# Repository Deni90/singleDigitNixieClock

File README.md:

# Single Digit Nixie Clock

A small project combining ESP32 with a vintage Soviet Nixie tube from the 70’ to create an artistic clock.
Originally developed on ESP8266/Arduino, now evolved to ESP32 with ESP-IDF for greater performance and stability.

Huge thank you to **[PCBWay](https://www.pcbway.com)** for sponsoring this project!

For more details follow project logs on: **[my personal blog](https://deni90.github.io/projects/singledigitnixieclock/)** or **[hackaday.io](https://hackaday.io/project/202115-single-digit-nixie-clock)**

Some of the key features:
- Shows current time (hours and minutes) on a single nixie tube.
- Configurable RGB LED backlight lights up the nixie tube every second.
- USB powered.
- Hosts a web server for easy setup & configuration.
- Synchronises time with NTP server.

Operating modes:
- AP mode
  - This mode is hosting a dedicated open wifi network called `NixieClock`. Its main purpose is to use it for first time setup to update wifi configuration. In addition, this mode will be activated when the clock is not able to connect to a configured network. Clock hosts a captive portal. A configuration page will be opened automatically upon connecting to `NixieClock` network.
- Client mode
  - In this mode the clock is connected to a configured wifi network. If there is internet access, the clock will synchronize its RTC with NTP server at startup and then every hour periodically.

In both modes, the configuration page is easily reachable on the following URL: `<HOSTNAME>.local`. There is no need to keep track of the IP address, the clock is hosting Multicast DNS (mDNS) server. mDNS is supported by Chrome and Safari browsers out of the box.

By default, the `HOSTNAME` is set to `mynixieclock`.

## Firmware

This project started on ESP8266 with the Arduino framework, which was great for fast prototyping. However, the reliance on third-party libraries often led to instability and crashes.

To ensure long-term support and stability, the project was migrated from the now-obsolete ESP8266 to the ESP32, using ESP-IDF in C++.

This move provides:
- A robust and stable firmware base.
- Full access to ESP32’s hardware features.
- Use of official ESP-IDF components

### REST API

| End point | Method | Body (JSON) | Description |
| - | - | - | - |
| /api/v1/led/led_info | GET | {<br>&nbsp;&nbsp;&nbsp;&nbsp;“R”: <0-255>,<br>&nbsp;&nbsp;&nbsp;&nbsp;“G”: <0-255>,<br>&nbsp;&nbsp;&nbsp;&nbsp;“B”: <0-255>,<br>&nbsp;&nbsp;&nbsp;&nbsp;“state”: <0-2><br>} | Get color and state of the backlight (RGB LED). |
| /api/v1/led/led_info | POST | {<br>&nbsp;&nbsp;&nbsp;&nbsp;“R”: <0-255>,<br>&nbsp;&nbsp;&nbsp;&nbsp;“G”: <0-255>,<br>&nbsp;&nbsp;&nbsp;&nbsp;“B”: <0-255>,<br>&nbsp;&nbsp;&nbsp;&nbsp;“state”: <0-2><br>} | Set color and state of the backlight (RGB LED). |
| /api/v1/clock/sleep_info | GET | {<br>&nbsp;&nbsp;&nbsp;&nbsp; “sleep_before”: \<value>,<br>&nbsp;&nbsp;&nbsp;&nbsp; “sleep_after”: \<value><br>} | Get sleep mode configuration. The time before and after (in minutes) the backlight will be turned off. |
| /api/v1/clock/sleep_info | POST | {<br>&nbsp;&nbsp;&nbsp;&nbsp; “sleep_before”: \<value>,<br>&nbsp;&nbsp;&nbsp;&nbsp; “sleep_after”: \<value><br>} | Set sleep mode configuration. |
| /api/v1/clock/time_info | GET | {<br>&nbsp;&nbsp;&nbsp;&nbsp;"tz_zone": "\<Geographic zone>",<br>&nbsp;&nbsp;&nbsp;&nbsp;“tz_offset”: “\<Proleptic TZ>",<br>&nbsp;&nbsp;&nbsp;&nbsp;"time_format": \<"12h" \| "24h"><br>} | Get time zone configuration |
| /api/v1/clock/time_info | POST | {<br>&nbsp;&nbsp;&nbsp;&nbsp;"tz_zone": "\<Geographic zone>",<br>&nbsp;&nbsp;&nbsp;&nbsp;“tz_offset”: “\<Proleptic TZ>",<br>&nbsp;&nbsp;&nbsp;&nbsp;"time_format": \<"12h" \| "24h"><br>} | Set time zone configuration |
| /api/v1/wifi/wifi_info | GET | {<br>&nbsp;&nbsp;&nbsp;&nbsp;"hostname": "\<HOSTNAME>",<br>&nbsp;&nbsp;&nbsp;&nbsp;“SSID”: “\<Wifi SSID>”,<br>&nbsp;&nbsp;&nbsp;&nbsp;"auth_type": \<"open" \| "wpa2" \| "wpa3">,<br>&nbsp;&nbsp;&nbsp;&nbsp;“password”: “\<base64 encoded password>”<br>} | Get wifi configuration. |
| /api/v1/wifi/wifi_info | POST | {<br>&nbsp;&nbsp;&nbsp;&nbsp;"hostname": "\<HOSTNAME>",<br>&nbsp;&nbsp;&nbsp;&nbsp;“SSID”: “\<Wifi SSID>”,<br>&nbsp;&nbsp;&nbsp;&nbsp;"auth_type": \<"open" \| "wpa2" \| "wpa3">,<br>&nbsp;&nbsp;&nbsp;&nbsp;“password”: “\<base64 encoded password>”<br>} | Set wifi configuration. | Set wifi configuration. |

### Front-end layout & design

Initially, the front end was implemented with jQuery mobile. Reason for choosing this framework was in its simplicity. It provides a simple way to create and control user interface components. One thing that always annoyed me was its low response time. It took too much time to load jQuery, jQueryMobile and theme resources. On top of this, this slow response time caused WDT resets.

One more thing, I just realised that  jQuery mobile project is deprecated since October 7, 2021. Huh, when it comes to web related technologies, it looks like I'm living under a rock...

To solve these issues, I opted to completely re implement the frontend using plain HTML, CSS and JavaScript. The end result looks almost the same as the previous design or even better. Responsiveness and stability increased significantly. The only drawback is now in maintenance and extension. It is required to implement everything manually.

## Design

Schematic and PCB are designed with KiCAD

### Control board

Control board is basically a re-packaged generic ESP32 board design connected with DS3231 real time clock and NCH8200HV high voltage boost module board.

#### Schematic

### Display board

Display board uses a CD4028 BCD-to-decimal decoder. Its purpose is to reduce the number of required GPIO pins from 10 to just 4 for showing digits from 0 to 9. Compared to dedicated BCD to decimal decoder nixie drivers (like K511ID1), the CD4028 is a widely spread component and it is available in SMD package. Since CD4028 has a voltage range from 3.0V to 15V it is not compatible with nixie tube’s operating voltage of 170V out of the box. This problem is solved with MMBTA42, a high voltage transistor, rated to more than 200V.

The rest of the display board consists of a WS2812B RGB LED and a pin header used to connect with the control board.

#### Schematic

## PCB manufacturing

A representative from **PCBWay** contacted me because he was deeply impressed by my project and offered to sponsor a batch of PCBs to test out their services.

Since I recently moved to KiCad, it was a perfect opportunity to try out the PCBWay Plug-in for KiCad. It provides a simple way to place an order in just a few clicks. There is no need to bother with exporting gerber files, everything is automated. You just need to update the PCB specification and fill in the shipping information on the webpage. That’s it.

The entire journey from placing the order to receiving the package took less than a week. Incredible! PCBWay did a superb job, PCBs are amazing. I am more than impressed.

## Enclosure design

3D model is made with Autodesk Fusion 360.

The end result is a simple box shaped design with holes for the nixie tube and USB connector.

## Third-party dependencies

This project includes `firmware/flash_data/frontend/zones.json` from https://github.com/nayarsystems/posix_tz_db, licensed under the MIT License.

## Resources

* [IN-14 Nixie tube datasheet](https://tubehobby.com/datasheets/in14.pdf)
* [NCH8200HV High Voltage DC-DC Booster module](http://omnixie.io/nch8200hv.html)
* [CD4028 datasheet](https://www.renesas.com/en/document/dst/cd4028bms-datasheet?srsltid=AfmBOoqU2NILPd5EzyLmpNgOihDv6LZo1jPMcaXfnR6dCclXbg2DF4TL)

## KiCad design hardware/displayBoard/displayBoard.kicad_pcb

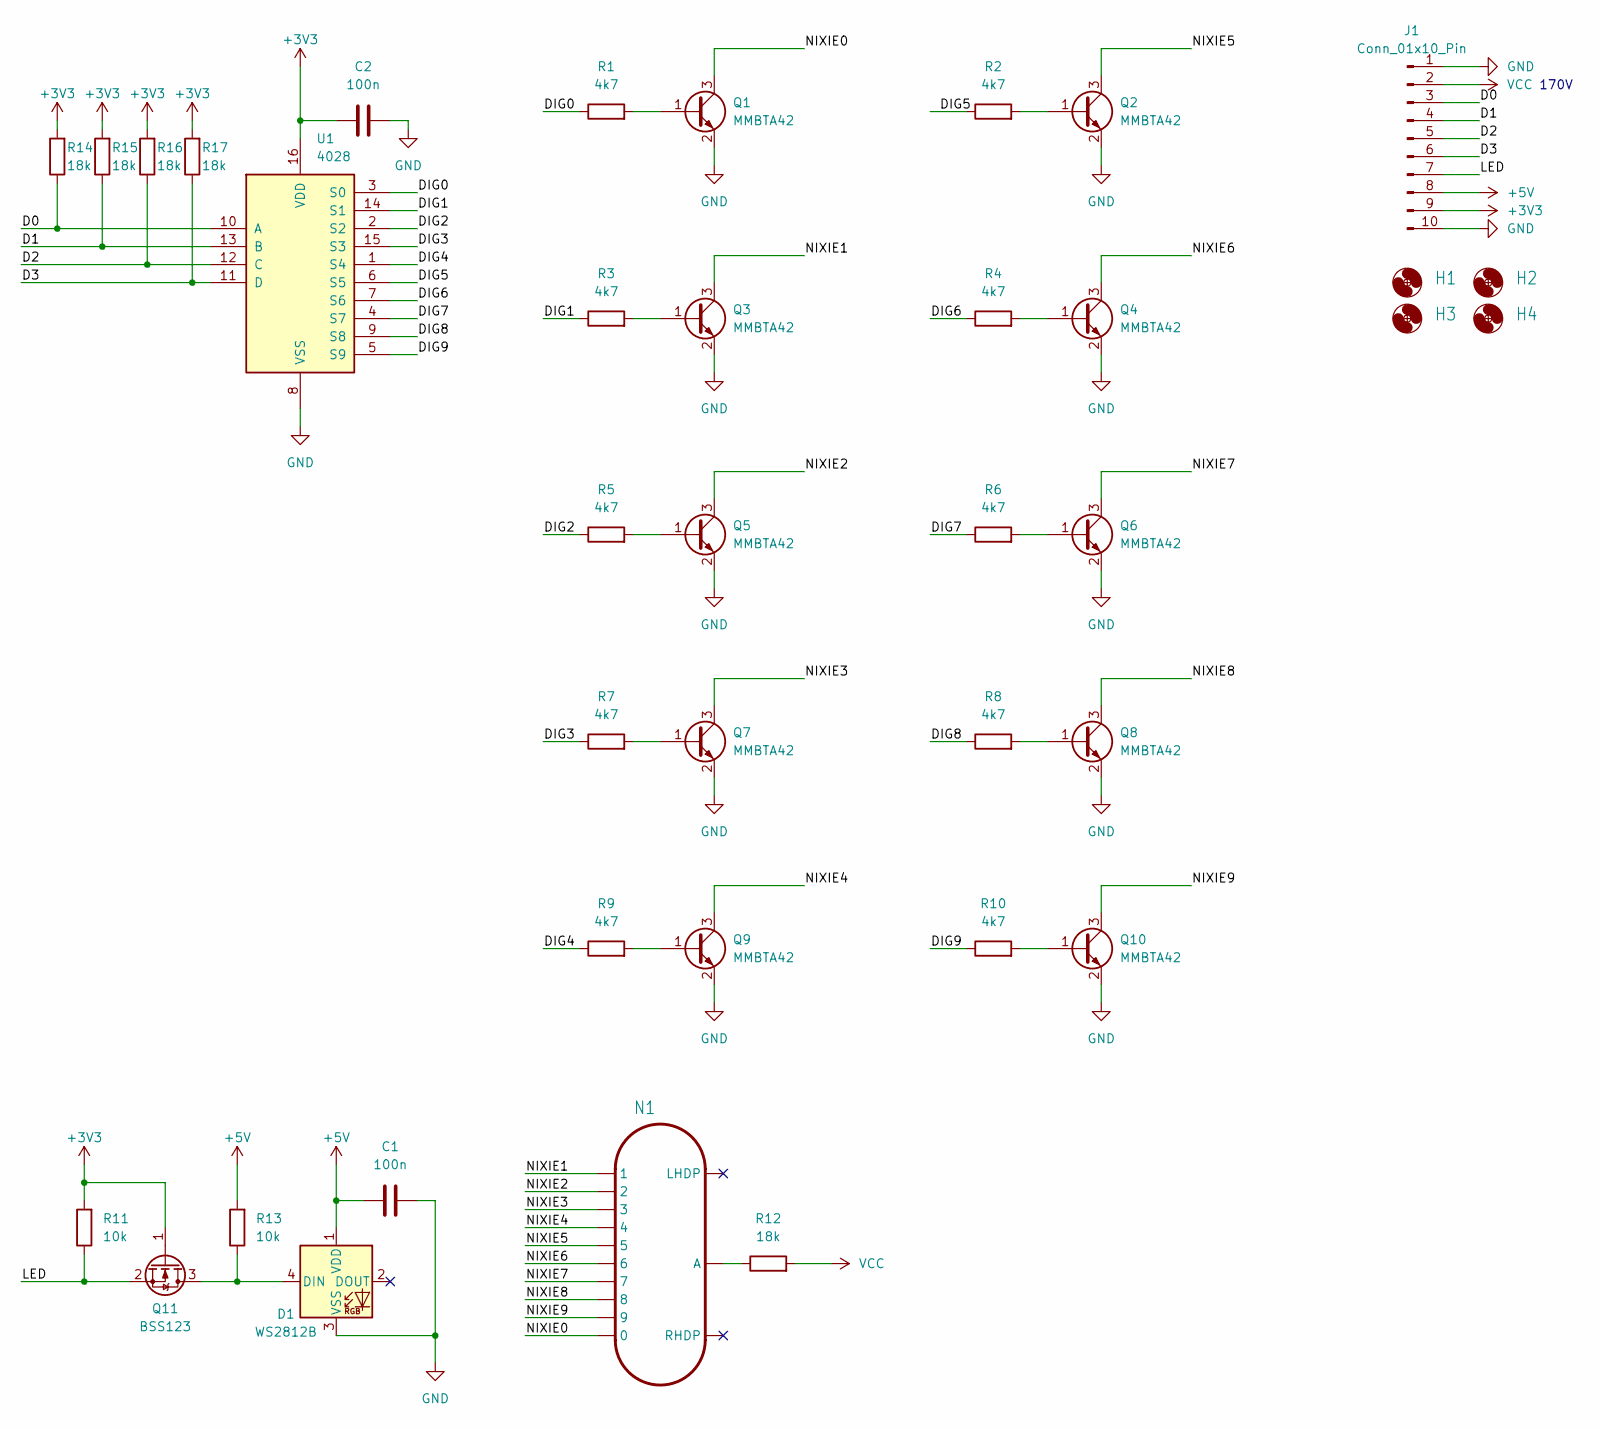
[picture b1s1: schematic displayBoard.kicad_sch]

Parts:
C1, C2: 100n; C_0603_1608Metric
D1: WS2812B; LED_WS2812B_PLCC4_5.0x5.0mm_P3.2mm
H1, H2, H3, H4: MountingHole_3.2mm_M3
J1: Conn_01x10_Pin; PinHeader_1x10_P2.54mm_Vertical
N1: IN-14
Q1, Q2, Q3, Q4, Q5, Q6, Q7, Q8, Q9, Q10: MMBTA42; SOT-23
Q11: BSS123; SOT-23
R1, R2, R3, R4, R5, R6, R7, R8, R9, R10: 4k7; R_0603_1608Metric
R11, R13: 10k; R_0603_1608Metric
R12, R14, R15, R16, R17: 18k; R_0603_1608Metric
U1: 4028; SO-16_3.9x9.9mm_P1.27mm

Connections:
+3V3: C2.1, J1.9, Q11.1 (G), R11.2, R14.2, R15.2, R16.2, R17.2, U1.16 (VDD)
+5V: C1.1, D1.1 (VDD), J1.8, R13.2
/D0: J1.3, R14.1, U1.10 (A)
/D1: J1.4, R15.1, U1.13 (B)
/D2: J1.5, R16.1, U1.12 (C)
/D3: J1.6, R17.1, U1.11 (D)
/DIG0: R1.1, U1.3 (S0)
/DIG1: R3.1, U1.14 (S1)
/DIG2: R5.1, U1.2 (S2)
/DIG3: R7.1, U1.15 (S3)
/DIG4: R9.1, U1.1 (S4)
/DIG5: R2.1, U1.6 (S5)
/DIG6: R4.1, U1.7 (S6)
/DIG7: R6.1, U1.4 (S7)
/DIG8: R8.1, U1.9 (S8)
/DIG9: R10.1, U1.5 (S9)
/LED: J1.7, Q11.2 (S), R11.1
/NIXIE0: N1.0, Q1.3 (C)
/NIXIE1: N1.1, Q3.3 (C)
/NIXIE2: N1.2, Q5.3 (C)
/NIXIE3: N1.3, Q7.3 (C)
/NIXIE4: N1.4, Q9.3 (C)
/NIXIE5: N1.5, Q2.3 (C)
/NIXIE6: N1.6, Q4.3 (C)
/NIXIE7: N1.7, Q6.3 (C)
/NIXIE8: N1.8, Q8.3 (C)
/NIXIE9: N1.9, Q10.3 (C)
GND: C1.2, C2.2, D1.3 (VSS), J1.1, J1.10, Q1.2 (E), Q2.2 (E), Q3.2 (E), Q4.2 (E), Q5.2 (E), Q6.2 (E), Q7.2 (E), Q8.2 (E), Q9.2 (E), Q10.2 (E), U1.8 (VSS)
unnamed: D1.4 (DIN), Q11.3 (D), R13.1
unnamed: N1.A, R12.1
unnamed: Q1.1 (B), R1.2
unnamed: Q2.1 (B), R2.2
unnamed: Q3.1 (B), R3.2
unnamed: Q4.1 (B), R4.2
unnamed: Q5.1 (B), R5.2
unnamed: Q6.1 (B), R6.2
unnamed: Q7.1 (B), R7.2
unnamed: Q8.1 (B), R8.2
unnamed: Q9.1 (B), R9.2
unnamed: Q10.1 (B), R10.2
VCC: J1.2, R12.2

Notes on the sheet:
170V

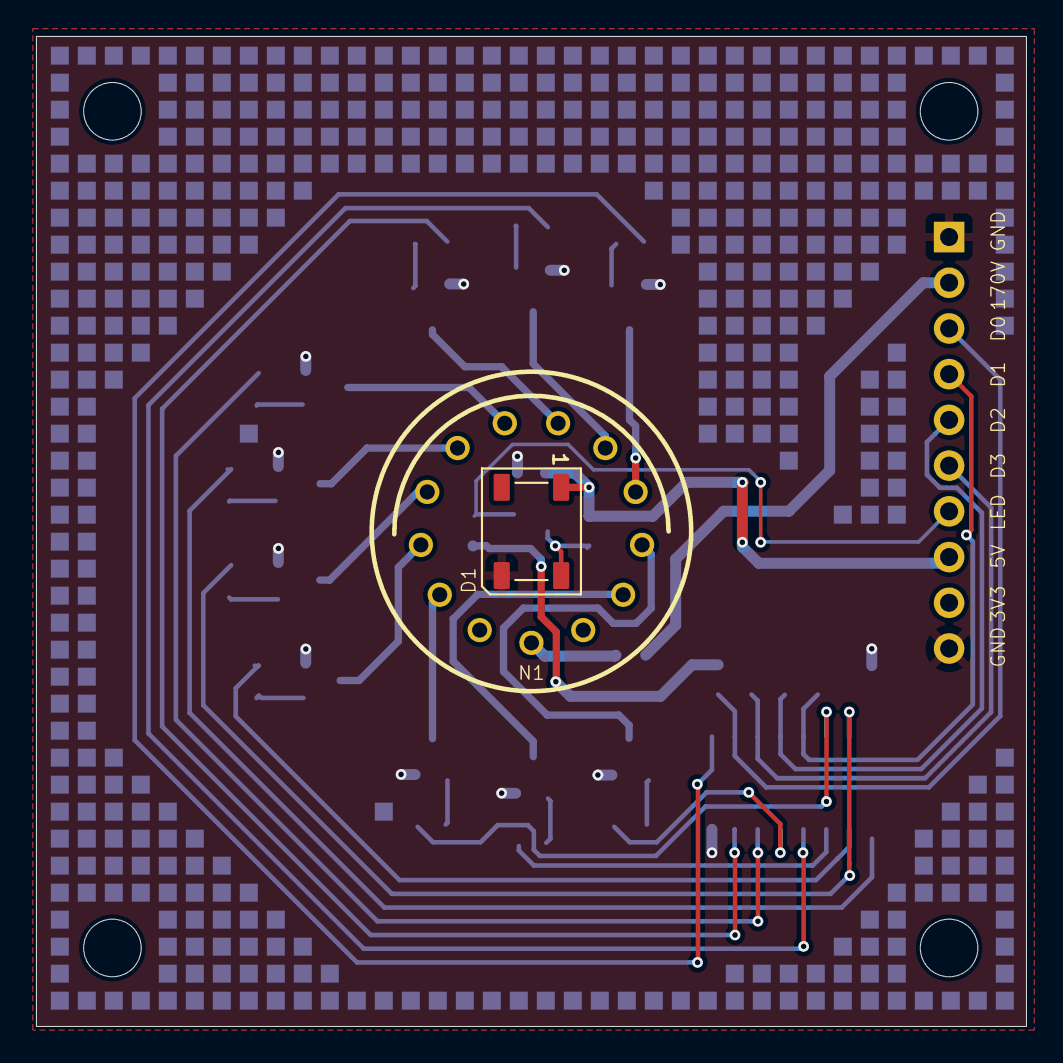
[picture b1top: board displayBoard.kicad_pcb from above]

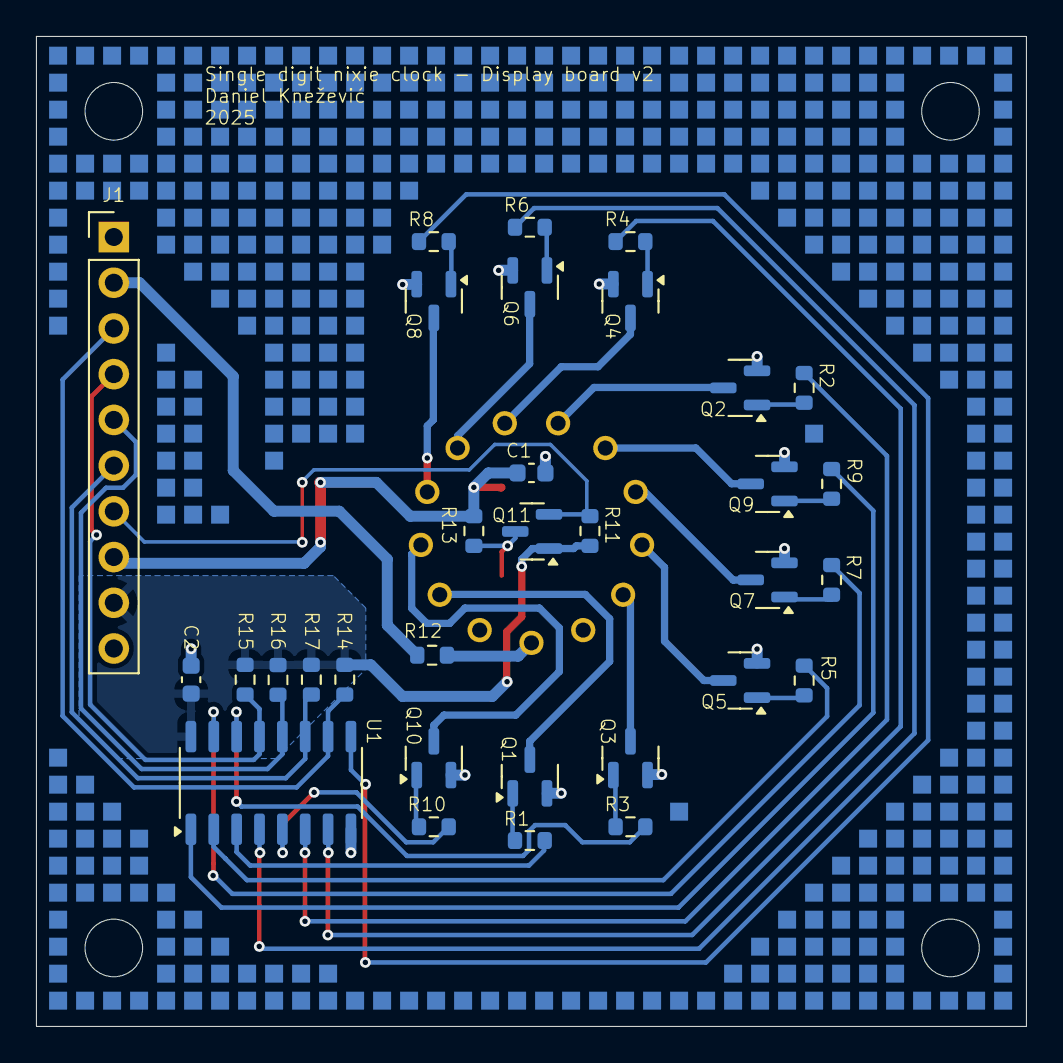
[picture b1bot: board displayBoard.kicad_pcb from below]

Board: 2 copper layers, 55.0 x 55.0 mm, 38 parts (32 on the bottom side), 41 nets.

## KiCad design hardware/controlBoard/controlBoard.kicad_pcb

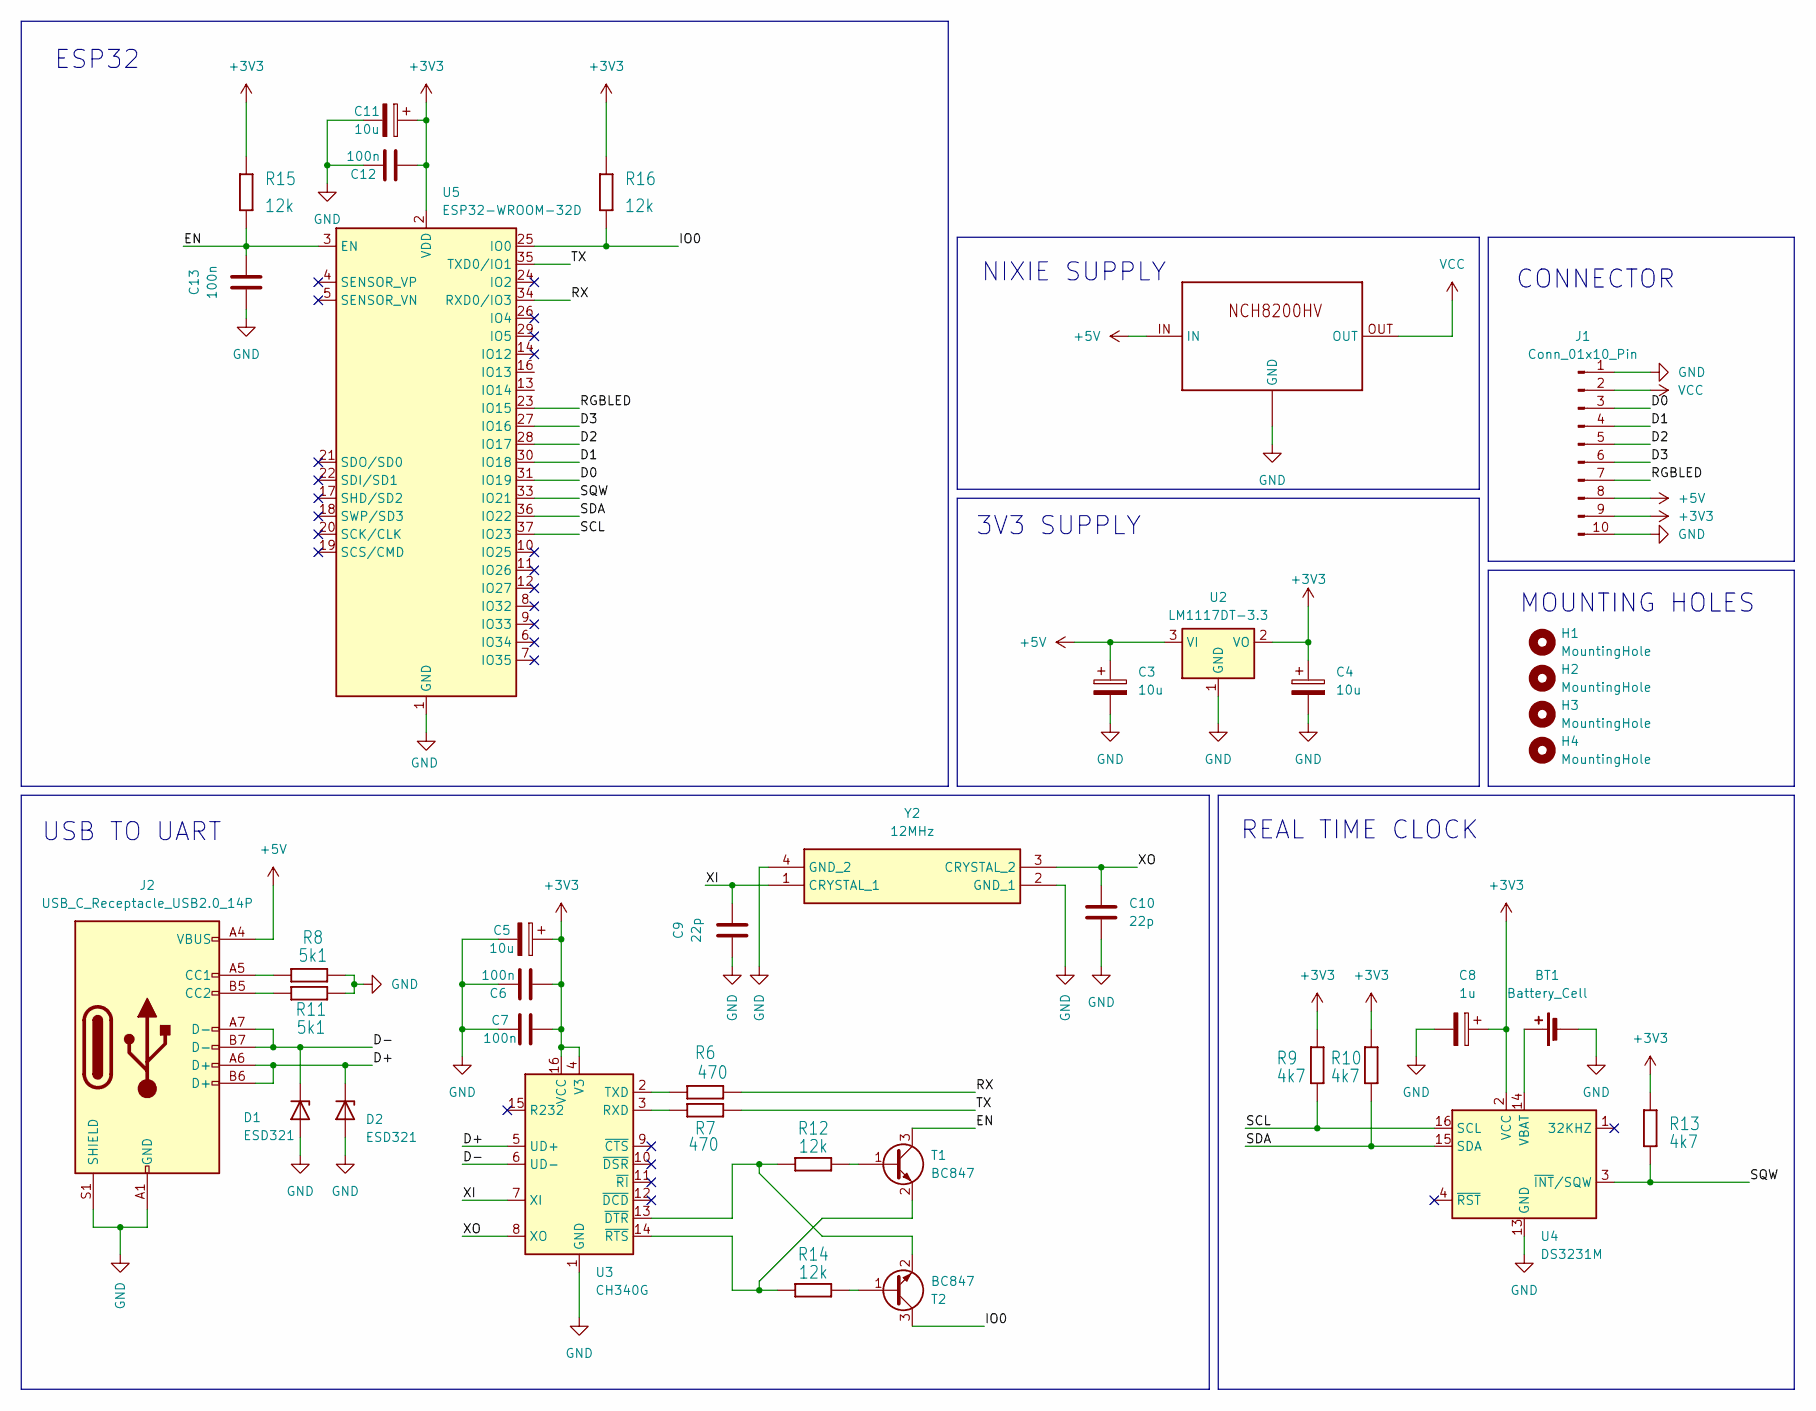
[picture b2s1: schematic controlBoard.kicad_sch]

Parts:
BT1: Battery_Cell; BatteryHolder_MYOUNG_BS-07-A1BJ001_CR2032
C3, C4, C5, C11: 10u; CP_EIA-3216-10_Kemet-I
C6, C7, C12, C13: 100n; C_0603_1608Metric
C8: 1u; CP_EIA-3216-10_Kemet-I
C9, C10: 22p; C_0603_1608Metric
D1, D2: ESD321; D_SOD-523
H1, H2, H3, H4: MountingHole; MountingHole_3.2mm_M3
J1: Conn_01x10_Pin; PinHeader_1x10_P2.54mm_Vertical
J2: USB_C_Receptacle_USB2.0_14P; USB_C_Receptacle_GCT_USB4105-xx-A_16P_TopMnt_Horizontal
R6, R7: 470; R_0603_1608Metric
R8, R11: 5k1; R_0603_1608Metric
R9, R10, R13: 4k7; R_0603_1608Metric
R12, R14, R15, R16: 12k; R_0603_1608Metric
T1, T2: BC847; SOT-23
U2: LM1117DT-3.3; TO-252-3_TabPin2
U3: CH340G; SOIC-16_3.9x9.9mm_P1.27mm
U4: DS3231M; SOIC-16W_7.5x10.3mm_P1.27mm
U5: ESP32-WROOM-32D; ESP32-WROOM-32D-no-keepout
UNK1: NCH8200HV
Y2: 12MHz; 405I35D25M00000; Mouser Part Number 774-405I35D25M00000

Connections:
+3V3: C4.1, C5.1, C6.1, C7.2, C8.1, C11.1, C12.1, J1.9, R9.2, R10.2, R13.2, R15.2, R16.2, U2.2 (VO), U3.4 (V3), U3.16 (VCC), U4.2 (VCC), U5.2 (VDD)
+5V: C3.1, J1.8, J2.A4 (VBUS), J2.A9 (VBUS), J2.B4 (VBUS), J2.B9 (VBUS), U2.3 (VI), UNK1.IN
/D0: J1.3, U5.31 (IO19)
/D1: J1.4, U5.30 (IO18)
/D2: J1.5, U5.28 (IO17)
/D3: J1.6, U5.27 (IO16)
/D+: D2.1 (K), J2.A6 (D+), J2.B6 (D+), U3.5 (UD+)
/D-: D1.1 (K), J2.A7 (D-), J2.B7 (D-), U3.6 (UD-)
/EN: C13.1, R15.1, T1.3 (C), U5.3 (EN)
/IO0: R16.1, T2.3 (C), U5.25 (IO0)
/RGBLED: J1.7, U5.23 (IO15)
/RX: R6.2, U5.34 (RXD0/IO3)
/SCL: R9.1, U4.16 (SCL), U5.37 (IO23)
/SDA: R10.1, U4.15 (SDA), U5.36 (IO22)
/SQW: R13.1, U4.3 (~INT/SQW), U5.33 (IO21)
/TX: R7.2, U5.35 (TXD0/IO1)
/XI: C9.1, U3.7 (XI), Y2.1 (CRYSTAL_1)
/XO: C10.1, U3.8 (XO), Y2.3 (CRYSTAL_2)
GND: BT1.2 (-), C3.2, C4.2, C5.2, C6.2, C7.1, C8.2, C9.2, C10.2, C11.2, C12.2, C13.2, D1.2 (A), D2.2 (A), J1.1, J1.10, J2.A1 (GND), J2.A12 (GND), J2.B1 (GND), J2.B12 (GND), J2.S1 (SHIELD), R8.2, R11.2, U2.1 (GND), U3.1 (GND), U4.5 (GND), U4.6 (GND), U4.7 (GND), U4.8 (GND), U4.9 (GND), U4.10 (GND), U4.11 (GND), U4.12 (GND), U4.13 (GND), U5.1 (GND), U5.15 (GND), U5.38 (GND), U5.39 (GND), UNK1.GND@1 (GND), UNK1.GND@2 (GND), Y2.2 (GND_1), Y2.4 (GND_2)
unnamed: BT1.1 (+), U4.14 (VBAT)
unnamed: J2.A5 (CC1), R8.1
unnamed: J2.B5 (CC2), R11.1
unnamed: R12.2, T1.1 (B)
unnamed: R14.1, T1.2 (E), U3.14 (~RTS)
unnamed: R14.2, T2.1 (B)
unnamed: R12.1, T2.2 (E), U3.13 (~DTR)
unnamed: R7.1, U3.3 (RXD)
unnamed: R6.1, U3.2 (TXD)
VCC: J1.2, UNK1.OUT

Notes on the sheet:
ESP32
CONNECTOR
NIXIE SUPPLY
USB TO UART
3V3 SUPPLY
REAL TIME CLOCK
MOUNTING HOLES

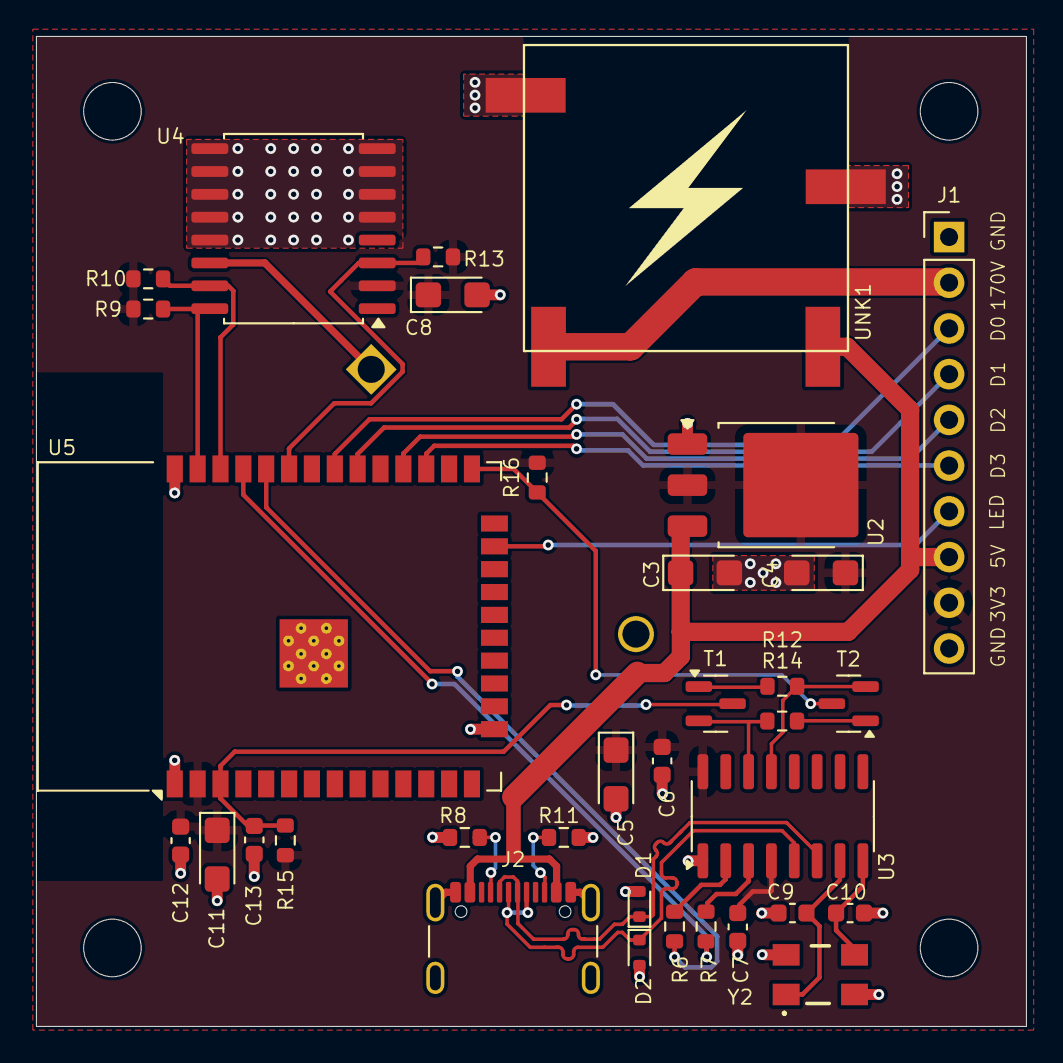
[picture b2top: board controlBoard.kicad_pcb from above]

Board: 2 copper layers, 55.0 x 55.0 mm, 39 parts (1 on the bottom side), 29 nets.

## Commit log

2020-04-23 Updated README file
2020-05-06 Refactored usage of timers and enabled SQW of DS3231
    - changed led pin to D3
    - enabled interrupt for SQW
2020-05-06 Renamed UpdateState to Update in LedController.
2020-05-06 Implemented BCD 2 decimal decoder
2022-04-01 Added display board schematic & PCB design
2022-04-01 Moved displayBoard under schematic folder
2022-04-06 Removed white spaces from LedController
2022-04-06 Separated led info from led controller
    Led information like color and state are moved to a separate module.
2022-04-06 EEPROM hangling is moved under ConfigStore module
    Config store module is responsible for loading and saving device's
    configurations like led color, led status, ...
2022-04-06 Created ClockFace module to handle time animations.
    Main has been refactored by moving nixie & led handling into a
    sepatare module.
2022-04-06 Adafruit_NeoPixel is moved under LedController
2022-04-06 Defines converted to constexpr & added splash screen
2022-04-07 Updated LedState to have ON, OFF and FADE states
2022-04-11 Removed vscode folder
2022-04-11 Implemented a web server by using jquery mobile
    - REST server has been replaced by ESP8266WebServer
    - Web page is stored on flash by using LittleFS file system
    - Backlight control has been implemented with ClockInterface
2022-04-12 Implemented set color in web server
2022-04-12 Refactored LED handling
    - removed alpha from classes and interfaces
    - fading is simplified by modifying only the brightness
2023-12-27 Create an adapter to fix showing wrong digits
    Create In18NixieTube to adapt BCD2DecimalDecoder so that correct
    digits are shown on the nixie tube.
    For some reason the pinout of the IN-18 tube does not match with
    Eagle's component.
2023-12-27 Fine tune animation timeouts and reverse intro
2023-12-28 Reformat code
2023-12-28 Move source to firmware folder
2023-12-28 Add backlight configuration to server
    - enable setting backlight brightness, mode and color
2023-12-28 Add set current time to REST API
2023-12-28 Add clang-format & reformat code
2023-12-29 Refactor WebServer
    - Replace ESP8266WebServer with AsyncWebServer
    - Simplify module by removing singleton
2023-12-29 Add an option for pulsing LED
2023-12-29 Remove AlwaysBreakAfterReturnType from clang-format
2023-12-29 Make truthTable const
2023-12-29 Remove formatSwitch from HTML page
2023-12-29 Show time after it is updated via REST API
    - Refactor ClockFace to accept the number of repeats whren showing time
2023-12-30 Rename In18NixieTube module to In14NixieTube
2024-01-03 Reduce the size of the controll board
2024-01-03 Add README & images to CB
2024-01-03 Add control board schematic
2024-02-01 Supply CH340 with 3V3 to fix ESP programming issue
    In order to properly communicate with ESP it is required to use CH340
    USB to serial in 3V3 mode.
2024-02-02 Add ESD protection to USB data lanes
2024-02-02 Add title to PCBs
2024-02-02 Update schematic images
2024-10-07 Add doxygen comments
2024-10-07 Remove ci variable
2024-10-07 Refactor In14NixieTube by encapsulating BCD2DecimalDecoder
2024-10-07 Change SSID
2024-10-10 Simplify WebServer by combining paths
    - Combine backlight related paths into Get/Set methods.
    - Add lock to led controller to prevent updating led state while showing
    time.
    - Update index.html to use the new REST API.
2024-10-10 Rename counter to secondsCounter and fix buffer size
2024-10-16 Refactor HandleGetLedInfo
    - Use JsonDocument instead of StaticJsonDocument
    - Use String instead of char buffer
    - Use serializeJson instead of serializeJsonPretty to shorten the JSON
    message
2024-10-16 Move ShowTime to HandleInterrupt interrupt routine
2024-10-28 Rename label to Color preview
2024-10-31 Move implementation of ClockInterface to NixieClock
    - Move implementation of ClockInterface to ClockFace
    - Remove NixieClockInterface class
    - Rename ClockFace class to NixieClock
2024-11-01 Add headings to tabs
2024-11-01 Fix OnGetLedInfo to get info from ConfigStore
2024-11-01 Update time format in prints
2024-11-01 Check for NULL in WebServer::Handle functions
2024-11-01 Rename backlight to ledInfo
2024-11-02 Implement sleep mode feature
    Sleep mode turns off the led and nixie tube for a configured time period
2024-11-02 Rename Load/StoreLedConfiguration to Load/StoreLedInfo
2024-11-02 Fix updating led info while in sleep mode
2024-11-05 Add readme file to the project
2024-11-17 Replace image with gif
2024-11-18 Update readme files
2024-12-28 Update dependencies
2024-12-28 Refactor ConfigStore to use LittleFS
    - Replace EEPROM with json config files
2024-12-28 Add ToJson() to LedInfo and SleepInfo classes
    - Update ConfigStore and WebServer to use ToJson().
2024-12-28 Make prints in setup() pretty
2024-12-28 Load Wifi SSID and password from a JSON file
2024-12-28 Move web server files to a dedicated folder
2024-12-28 Add wifi tab to web page
    - Extend ConfigStore with SaveWifiInfo function.
    - Extend WebServer with /wifi GET and POST methods.
    - Update web page with a wifi tab.
2024-12-28 Fix colorBox init and currentTime label access
2024-12-30 Update firmware's readme file
2025-01-01 Add more comments to NixieClock::Handle
2025-01-01 Convert EaglePCB projects to KiCad
2025-01-06 Connect clock to a local wifi network
    - By default configure clock to use wifi in station mode.
    - Try to connect to the configured wifi network
    - If it is not possible to connect to a configured network switch to AP mode
    - Use different DnsServer for captive portal in AP mode
    - Use MDNS for station mode
2025-01-06 Remove 'ap' prefix from wifi tab
2025-01-07 Synchronise time via NTP
    - Create TimeInfo for storing time related configuration
    - Create TimeManager for getting time from NTP server
2025-01-07 Make time zone configurable via web server
2025-01-07 Remove printing out config and remove default wifi credentials
2025-01-11 Re-implement web server to improve performance and stability
    - Remove dependency to jQuery mobile
    - Use plain javascript for the front-end implementation
    - Define a cutom css style to follow existing UI design
    - Refactor WebServer REST api handling to use AsyncCallbackJsonWebHandler
    - Enable mDNS in AP mode
2025-01-11 Use usb type C connector and re-wire control board with KiCad components
2025-01-11 Remove formatting from config files
2025-01-11 Refactor *DNS usage
2025-01-12 Enter sleep mode right after config is updated
2025-01-12 Modify SleepInfo to use minutes and update frontend
2025-01-12 Re-wire control display with KiCad components
2025-01-12 Update images of new PCBs
2025-01-12 Update main readme file
2025-01-13 Add front-end section to README
2025-01-14 Describe operating modes
2025-01-16 Update control board with updated usb-c wiring
2025-01-18 Make hostname configurable via web app
2025-01-22 Add model diagrams to Readme
2025-01-30 Fix weird behaviour of the LED by adding a level shifter to DIN pin
2025-01-31 Match via sizes between two PCBs
2025-02-11 Update README with hackaday link and PCBWay sponsorship
2025-02-28 Add enclosure model to repo
2025-03-30 Replace agdl/Base64 with densaugeo/base64 library
2025-03-30 Replace PlatformIO with Makefile
    To simplify project setup, the Arduino core for ESP8266 and all dependencies are moved to be part of the project as git submodules. This way, there is no need to manualy download and setup Arduino ID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
2025-04-06 Make choice handling more generic
2025-04-06 Add support for daylight saving time
2025-04-09 Re-enable password sharing in HandleGetWifiInfo
2025-04-09 Setup AP mode when the wifi SSID is empty
2025-04-09 Log wifi SSID and hostname in setup()
2025-06-03 Update README with a finished product
2025-08-18 Remove C4 diagrams from README
2025-08-30 Use ESP32 instead of ESP8266
    - Re-route PCB to support ESP32
    - Fill top plane with +3v3
2025-08-30 Rename schematic folder to hardware
2025-08-31 Finalize PCB design
2025-09-06 Port firmware to ESP32
    - Replace Arduino with ESP-IDF
    - Remove third-party git submodules
    - Use built-in ESP-EDF components for Wifi, LED, mDNS, DNS, FS, HTTP server, ...
    - Simplify nixie clock's logic by using freeRTOS tasks
2025-09-06 Add LED animation to initialize function of LedController
    - test() function is iterating through RGB colors at startup
2025-09-06 Add REST API versioning
    - Refactor WebServer's REST API to include API version
    - Update front-end to use the new REST API
2025-09-06 Add pull-ups to BCD decoder inputs
    - Add pull-up resistors to BCD decoder to prevent turning on the nixie tube during boot
2025-09-06 Set tab button witdth based on number of tabs
2025-09-06 Fix typos in server.js
2025-09-06 Load data on when opening a tab
2025-09-06 Remove global variables from front-end code
2025-09-06 Use 'let' instead of 'var'
2025-09-06 Update README with control board schematic
2025-09-07 Add a decoupling cap to CD4028
2025-09-08 Check is sleep mode active during startup
2025-09-10 Refactor led controller's temporal led state handling
    - Remove "locking" mechanism and replace it with temporal state
2025-09-10 Fix comments
2025-09-10 Add support for showing 12 and 24 hour formats
2025-09-11 Move littlefs setup to ConfigStore class
2025-09-11 Move wifi handling to WifiManager module
2025-09-27 Reorganize doc
    - rename images
    - update README.md with new file names and alt text
2025-09-27 Cosmetic fix on control board schematic
2025-09-27 Update image for front-end design
2025-09-29 Add authentication type to Wifi
    Add authentication type to Wifi so that the user can choose between open, WPA2 or WPA3 types when configuring the connection to a Wifi network.
2025-09-29 Update README with REST API doc and new front-end conaining wifi changes
2025-10-03 Implement getting time from RTC if NTP is not available
    - Implement an I2C OOP wrapper around ESP-IDF's i2c_master
    - Implement get/set time for DS3231 RTC
    - Integrate RTC handling to NixieClock
2025-10-07 Fix auto-programming circuit issue
    - Add pullups to EN and IO0 pins.
    - Add 100nF ceramic capacitor between EN and GND to improve timimng.
2025-10-10 Add copper thief to the bottom layer of display board
2025-10-19 Update assembled PCB image
2025-11-02 Fix entering/exiting sleep mode
2025-11-12 Fix exiting sleep mode
    Always start loop task in initialize function, regardless of being in sleep mode.
2025-12-09 Make a RAII wrapper for a FreeRTOS mutex
    - The mutex wrapper is compatible with std::lock_guard.
    - Code has been updated to use the new mutex.
2025-12-18 Add missing partition table to project
2025-12-18 Add a bigger delay between animation intro and showing current time
